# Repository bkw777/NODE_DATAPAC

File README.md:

# NODE Systems DATAPAC
* [Documentation](#documentation)
* [Hardware](#datapac-hardware)
  * [Reproduction Schematic & PCB](#reproduction-schematic--pcb)
  * [Theory of Operation](#theory-of-operation)
  * [Battery](#battery)
  * [Upgrading 128K to 256K](#upgrading-to-256k)
  * [Model Compatibility](#model-compatibility)
* [Software](#software)
  * [BASIC](#basic)
<!-- 
  * [RAMDSK](#ramdsk)
    * [Installation](#installing-ramdsk)
    * [Usage](#using-ramdsk)
  * [NBOOT](#nboot)
  * [RAMPAC Inspector](#rampac-inspector)
  * [XOS-C](#xos-c)
  * [N-DKTR](#n-dktr)
  * [NODE-PDD-Link](#node-pdd-link)
  * [NDEXE](#ndexe)
  * [RAMPAC Diagnostic](#rampac-diagnostic)
-->
* [MiniNDP](#minindp)
<!--
  * [PCB & BOM](#minindp-pcb--bom)
  * [Cover](#minindp-cover)
-->

This repo documents the NODE Systems [DATAPAC](PICS/DATAPAC/), [rampac](PICS/rampac/), and a new clone, the [MiniNDP](#minindp).

The NODE Systems DATAPAC/rampac was a popular ram disk peripheral for TRS-80 / TANDY Models 100, 102, & 200 computers.

The schematic and PCB below documents the DATAPAC.

rampac is a smaller later version of the same device that uses fewer larger sram chips and replaces most of the discrete logic IC's with a single PLD, but functions exactly the same.

Here is some disorganized [INFO](software/) mostly gathered from the [M100SIG archive](https://github.com/LivingM100SIG/Living_M100SIG) and [club100](http://www.club100.org).

TLDR: To use the hardware, install [RAMDSK](software/RAMDSK), and what you get is a ram disk of 128k to 1M depending on model and installed ram.

# Documentation
The original text file manual [RAMDSK.DO](ROM/100/RAMDSK.DO).  
The [NODE ROM](ROM) that came with the unit generates this file when formatting a device.

There are also some discussions in the [M100SIG archive](https://github.com/LivingM100SIG/Living_M100SIG) and Paul Globmans software on [club100](http://www.club100.org/library/libpg.html).  
Most of these are collected in [docs](docs).  
See also the docs for the various bits of [software](software).

Other References  
* "Database management with both the Node RAMPAC & DATAPAC."  
  Alspaugh, Ron - [Portable 100, Nov 90:8-11](https://archive.org/details/P100-Magazine/1990-11/page/8/)  
* "Node utility mini-extravaganza! Here are two special programs for Node Datapac/RAMPAC users."  
  Globman, Paul - [Portable 100, Dec 90:19-20](https://archive.org/details/P100-Magazine/1990-12/page/18/)  

# DATAPAC Hardware
## Reproduction Schematic & PCB
This is a new drawing but aims to reflect the original actual device as exactly as possible.  
It's meant to be a form of documentation or reference describing the original hardware as it was.  
For instance, the ungrounded inputs on the 161's, the inconsistent thickness of power traces, the fact that only 1 of the 2 bus VDD pins is connected, the VCC trace that almost touches one of the mounting screw heads, etc, are all exactly as in the original.  
(I added a fiber washer to that screw in my units after noticing that. The case is not connected to ground, but still...)  

For a historical reproduction version of the original PCB (minus the NODE copyright mark), see: NODE_DATAPAC_256K_historical_reproduction.kicad_pro

For a version of the original PCB that still uses the same components and fits in the same case, but cleans up a few things, see: NODE_DATAPAC_256K_bkw.kicad_pro

PCB TOP

PCB BOTTOM

The original PCB has no silkscreen. This image has silkscreen added to show where the components from the schematic go.

<!--
## Updated Replacement PCB that fits the original case

Uses all the same through-hole parts, fits in the original enclosure, improves the trace routing a little, for example moving that VCC line away from that screw head, GND traces replaced by zone fills, thicker and all the same size vcc lines, decoupling caps, silkscreen.  

-->

## Theory of Operation
The circuit has 2 functions, SELECT-BLOCK and READ/WRITE-BYTE, controlled by the internal active-low signals /BLOCK and /BYTE.

The U4 HC138 monitors four lines from the bus, `/Y0` `(A)` `A8` `A9`, and based on that asserts either `/BLOCK` or `/BYTE` or neither.  
If neither /BLOCK nor /BYTE is asserted then the bus traffic has no effect on any of the other chips.

The 3 HC161 form a 0-1023 counter, setting SRAM address bits A0-A9.  
Call this the byte-number or byte-position counter or offset.

The HC374 sets SRAM address bits A10-A17 from the bus data bits AD0-AD7, and latches that value on its outputs until triggered to update to a new value.  
Call this the block-number or block selector.

The U5 HC138 converts 3 bits of the block-number into 1 of 8 chip-select to select 1 of 8 32K SRAM chips,  
and also monitors both /BYTE and RAMRST and disables all ram while either /BYTE or RAMRST is high.

----

### SELECT-BLOCK
When /BLOCK goes low:
* SRAM A0-A9 are reset to 0  (byte-position counter is reset to 0)
* BUS AD0-AD7 are copied to SRAM A10-A17  (bus data lines AD0-AD7 select a block-number)

When /BLOCK goes high:
* SRAM A10-A17 are held latched at whatever they were set to  (block-number is locked in until next /BLOCK)

----

### READ-BYTE / WRITE-BYTE
When /BYTE goes low:
* SRAM is enabled  (bus data lines AD0-AD7 read from or write to the current address in SRAM)

When /BYTE goes high:
* SRAM is disabled
* A0-A9 are incremented by 1 (byte-position, thus the current address in SRAM, is advanced to the next byte)

----

The byte-number and block-number combine to form the current address in SRAM at any given time.  

The device provides up to 256 blocks (8-bit block-number) of 1024 bytes each (10-bit byte-number).

The host computer first does a SELECT-BLOCK to select a block number from 0-255, then does READ-BYTE or WRITE-BYTE to read or write one byte of data at byte number 0 in that block, then repeats the BYTE operation up to 1023 more times to read or write up to all 1024 bytes in the block.  

If you read or write more than 1024 times without selecting a new block, the byte-number counter just rolls over to 0 again.

You can also mix reads and writes in the same block. Each read OR write advances the byte position the same way each time, regardless if the previous operation was a read or a write. For instance in order to skip over 64 bytes without modifying them and then start writing at the 65th byte, you would read-and-ignore 64 times and then start writing.

"ramdisk" is an appropriate term because the device actually does operate like a disk even though it has no brains or firmware. The block-select latch acts like a track or sector address, and the binary counter acts like a disk or tape head reading or writing a sequential stream of bytes.

Later versions of RAMPAC were offered with 384k or 512k by adding a second bank of up to 256k, and later versions of RAMDSK.CO know how to access the 2nd bank.

In 512K units, the extra 256K is accessed by the state of bus address line A10 during a SELECT-BLOCK operation.  
SELECT-BLOCK with BUS_A10 low accesses bank0, with BUS_A10 high accesses bank1.  
All other aspects are the same, so accessing bank0 on a a 512K device is the same as accessing the only bank on a 256K device.  Old software is still compatible with bank0 on new hardware, new software is still compatible with old hardware.

[What this all means from the host computer software side of things](https://github.com/bkw777/NODE_DATAPAC?tab=readme-ov-file#low-level-direct-access-using-only-basic)

## Battery
The original battery is no longer made, and the modern cross-reference is almost 2mm taller and does not fit inside the enclosure.

NODE Systems themselves used to perform an update to older units to replace the original rechargeable NiCD cell with a non-rechargeable lithium cell which was supposed to last about 5 years.

The change is simple and easy, and the parts are common. You just remove the old battery and the 200 ohm resistor, and replace them with a CR2032 holder and a diode. That's it. Both parts fit and solder right in the same locations where the old parts came out. Point the diode stripe away from the battery, just like the other diode that is right there next to it. Any standard diode will do. Schottky is not recommended because the reverse leakage is not good for a lithium cell. Another 1N4148 like the one that's already there is perfect.  
This should give at least 4 years of memory.  
(The original NiCD battery may have only lasted as little as a few months per charge according to a review in the archives. So the coin cell mod is not merely more conveniently available with current parts, it's an improvement.)

BEFORE

AFTER

STEPS

If you wish to keep using a rechargeable battery, then one suitable option is FL3/V80H. That is 3 16x5.8mm NiMH button cells in a flat in-line pack with wire leads. It fits perfectly in the space next to the ribbon cable. It needs to be secured with hot glue or foam mounting tape, and connected with wires run to the original battery location.  

The charging circuit is utterly basic, so do not connect any other type of battery except NiCD or NiMH.  
You can use any cell form factor and any larger or smaller mAh capacity, but must be 3.6v and only NiCD or NiMH chemistry.

## Upgrading to 256K
A 128k unit may be upgraded to 256k by just adding 4 more SRAM chips piggy-backed onto the existing chips.

The PCB has 4 DIP-28 footprints for the SRAM chips.  
Each DIP-28 footprint also has an extra via close to pin 20.

A 128k unit has a low-power 62256 installed in each footprint, and nothing connected to the via near pin 20.

To get 256k, a second set of chips are soldered piggyback on top of the first four.  
All pins except pin 20 (chip-select) are simply soldered to the chip below.  
Pin 20 is bent out and connected to the extra via on the pcb (with a short bit of wire to reach) and not connected to the chip below.  

No other parts or changes are needed to upgrade an existing 128k unit to 256k.

Any 62256 will work, but for old parts you want the low-power version for standby battery life.  
New parts already naturally have as low or lower standby current than the low-power versions of old parts even if they don't say "low power".  
Old standard: HM62256    70uA  
Old lowpower: HM62256LP  4uA  
Old lowpower: P51256SL   2uA  
New standard: AS6C62256  1uA

The same is true for rampac. Except:  
 - single 128k sram chip, ex: AS6C1008
 - chip-select is pin 30

## Model compatibility  
Originally only North-American Models 100, 102, & 200 were ever supported.  
Kyotronic KC-85 and Olivetti M-10 are also supported today because RAMDSK has been disassembled and ported, and the assembly source means the international models could be added as well.  
The device is not compatible with NEC PC-8201/PC-8300.

Although the DATAPAC was primarily designed for Model 102 & 200, the crimp-on boxed male IDC pin header on the cable does not actually fit into a 200 without enlarging the opening around the bus connector on the 200. If you want to connect an original DATAPAC to a 200 without hacking up the 200's case or modifying the DATAPAC cable, you can build a small [adapter](ref/T200_adapter.jpg) by just soldering a [male](https://www.digikey.com/en/products/detail/sullins-connector-solutions/SBH11-PBPC-D20-ST-BK/1990068) & [female](https://www.digikey.com/en/products/detail/sullins-connector-solutions/SFH11-PBPC-D20-ST-BK/1990093) solder-type 2x20 boxed pin headers back to back. The solder box header does fit in the opening.

The DATAPAC case says "102/200", but it also works on Model 100, K85, and M10 with the right adapter cable. It's electrically compatible with everything but NEC.

For 100 & K85 the cable is just an IDC-DIP-40 aka "DIP-40 wire-to-board" connector and a standard 2x20 female IDC connector, both crimped onto a 40-pin ribbon cable about 8 inches long.  
[The Model 100 adapter part](https://github.com/bkw777/TRS-80_Disk_Video_Interface_Cable/blob/main/README.md#part-3---model-100-adapter) of this [3-part Disk/Video Interface Cable](http://tandy.wiki/Disk/Video_Interface:_Cable) is the same thing.

For Olivetti M-10 the cable is even simpler, a standard female to female IDC 40-pin ribbon cable.

[MiniNDP](#minindp) fits directly on both 102 and 200 with no adapter or cable, or M10 with a female-female ribbon cable at least 5 inches long.

[MiniNDP_u1M](#minindp-u1m---for-model-100-or-kyotronic-kc-85) fits directly in the bus socket of 100 or K85 with no adapter or cable, and the cover can even be closed over it.

# Software

 - [NODE ROM](ROM)  
 - [RAMDSK.CO](software/RAMDSK)  
 - [XOS-C](http://www.club100.org/library/libpg.html) ("sort of an OS" for the Model 200, does not require a rampac but leverages one if available. [Several of the NODE utils from the M100SIG require XOS-C.](software/Requires_XOS-C/))
 - [other](software)  

Originally these shipped with an [OPTION ROM](ROM) from NODE called RAMDISK.

Later, Paul Globman wrote [RAMDSK.CO](software/RAMDSK), and that was eventually licensed by NODE and shipped with new units.  

Later still, RAMDSK was updated with 2 changes:  
 - automatic repair of a corrupted format stamp on start-up  
 - support for 512k in 2 banks of 256k (RAMPAC & EXTRAM)

Recently, RAMDSK has been updated yet further:  
- disassembled to produce assembly source  
- ported to Kyotronic KC-85  
- ported to Olivetti M-10  
- support for 4 banks  
- format on demand from Label button  
- added safety confirmation to format & repair  
- removed dead code

Some other software culled from the [M100SIG archive](https://github.com/LivingM100SIG/Living_M100SIG) and [Club100](https://www.club100.org) are collected here in the [software](software) directory.  

## BASIC
How to access the hardware from BASIC.

### High level file operations using CALLable machine language routines
See [RAMDSK.DO](ROM/100/RAMDSK.DO) for the NODE ROM routines.  
See [RAMDSK.TIP](software/RAMDSK/RAMDSK.TIP) for the RAM100.CO/RAM200.CO routines.  
But note, the addresses in RAMDSK.TIP are incorrect for RAMDSK v2. We don't have a copy of RAMDSK v1 for 100 but we do for 200. So you can't follow those directions exactly except with RAMDSK v1 on 200.  

The latest RAMDSK built from the new source includes *.calls files that give the current addresses to the routines in those binaries, but actually using them has not been tested.

### Low level direct access using only BASIC
There are two low level operations that you use to access the device,  
BLOCK and BYTE, and each of those has two variations, for four total ops.

Select a BLOCK from BANK 0  
`OUT 129,n`  
Selects block# **n** (0-255) in bank 0, and resets the byte position to 0.

Select a BLOCK from BANK 1  
`OUT 133,n`  
Selects block# **n** (0-255) in bank 1, and resets the byte position to 0.

Read a BYTE  
`INP(131)`  
Reads the byte at the current byte position, and advances the byte position by one.

Write a BYTE  
`OUT 131,n`  
Writes the value **n** (0-255) to the current byte position, and advances the byte position by one.

The first read or write after selecting a block# applies to byte #0 of that block.  
The byte position advances by one after each read or write, so the next read or write will be byte #1, then byte #2, etc up to 1024.  
If you read or write more than 1024 times without selecting some other block, the byte position just rolls over to 0 again.

The position counter advances the same whether reading or writing.

Since the device can only read or write a single unsigned byte at a time, it's most efficient to use integer variables.  
Use the % suffix or DEFINT: `B%=INP(131)` or `DEFINT B : B=INP(131)`

The general sequence is always:  
1 - select a bank+block  
2 - read/write byte 0-1024 times

To seek to an arbitrary offset before reading or writing, read-and-ignore that many bytes.

For instance, in RBOOT.DO, to skip over the first 16 bytes of the block, it does `FORA=0TO15:N=INP(131):NEXT`  
N is not actually used, it's just reading 16 times and ignoring the data. This just advances the byte position counter to get from byte #0 past the 10-byte RAMDSK header and 6-byte .CO header to the start of the .CO executable data.

Examples

Select bank 0 block 0  
`OUT129,0`

read a byte, which will be byte #0 of this block  
`INP(131)`

Read and print the ascii of all the bytes in bank 0 block 2.  
(this will mess up the display from control bytes if there is a binary .CO file in this block)
```
10 OUT 129,2
20 FOR I=0 TO 1023
30 PRINT CHR$(INP(131));
40 NEXT
```

Do the same but in bank 1  
change line 10 to:  
`10 OUT 133,2`

Manually repair the first two bytes of block 0 to mark the bank as being formatted without touching any of the data.  
This means:
1. Select bank0 block0  
2. write one byte, value 64  
3. write one byte, value 4

`OUT129,0:OUT131,64:OUT131,4`

(BTW you usually don't need to do this because RAMDSK.CO will do it for you.)

# MiniNDP

New design that functions the same as DATAPAC/rampac.

1 megabyte in 4 banks of 256k.

How to access all 4 banks:  
Select bank 0, block N: `OUT 129,N`  
Select bank 1, block N: `OUT 133,N`  
Select bank 2, block N: `OUT 137,N`  
Select bank 3, block N: `OUT 141,N`

Everything else works the same as normal DATAPAC/rampac.

## MiniNDP EZ1M - For Model 102 and 200

Unlike the original DATAPAC, this actually fits into the bus port on the Model 200 without having to hack it's case.

[MiniNDP.bom.csv](PCB/out/MiniNDP.bom.csv)

BOM: [DigiKey](https://www.digikey.com/short/m4h7bmh0)  
[MiniNDP EZ1M_16 PCB @ OSHPark](https://oshpark.com/shared_projects/7Jpm6F6c)  
Cover: [MiniNDP_Cover.stl](COVER/out/MiniNDP_Cover.stl) -- [Cover @ JawsTec](https://shop.jawstec.com/3d-printed-minindp-cover_p658.php)  
[Both PCB & Cover @ PCBWAY](https://www.pcbway.com/project/shareproject/MiniNDP_mini_Node_DataPac_d08018c4.html)  

## MiniNDP u1M - For Model 100 or Kyotronic KC-85

BOM: [MiniNDP_u1M.bom.csv](PCB/out/MiniNDP_u1M.bom.csv)  
[MiniNDP u1M_038 PCB @ OSHPark](https://oshpark.com/shared_projects/XwUDgfQu)

## MiniNDP M10 - For Olivetti M-10

BOM: [MiniNDP_M10.bom.csv](PCB/out/MiniNDP_M10.bom.csv)  
[MiniNDP M10_40 PCB @ OSHPark](https://oshpark.com/shared_projects/pgmxRV8e)  
Cover for M10: [MiniNDP_Cover_M10.stl](COVER/out/MiniNDP_Cover_M10.stl) -- [M10 Cover @ JawsTec](https://shop.jawstec.com/3d-printed-minindpm10-cover_p657.php)  
Bus connector guide & filler plate for M10 [M10_BUS_Filler_Plate.stl](COVER/out/M10_BUS_Filler_Plate.stl)

## [Other Versions](MiniNDP_variants.md)  
[SL1M](MiniNDP_variants.md#sl1m---slim-1-meg) - slim 1 meg, all thin chips to make a thin card  
[T512](MiniNDP_variants.md#t512---tsop-128k256k512k) - TSOP 128k/256k/512k  
[EZ512](MiniNDP_variants.md#ez512---easy-build-512k) - SOIC 512k  
<!-- ["OG"](MiniNDP_variants.md#minindp-og) - 128k-512k, most like the original DATAPAC schematic, more parts and more difficult, but the parts are more common  -->

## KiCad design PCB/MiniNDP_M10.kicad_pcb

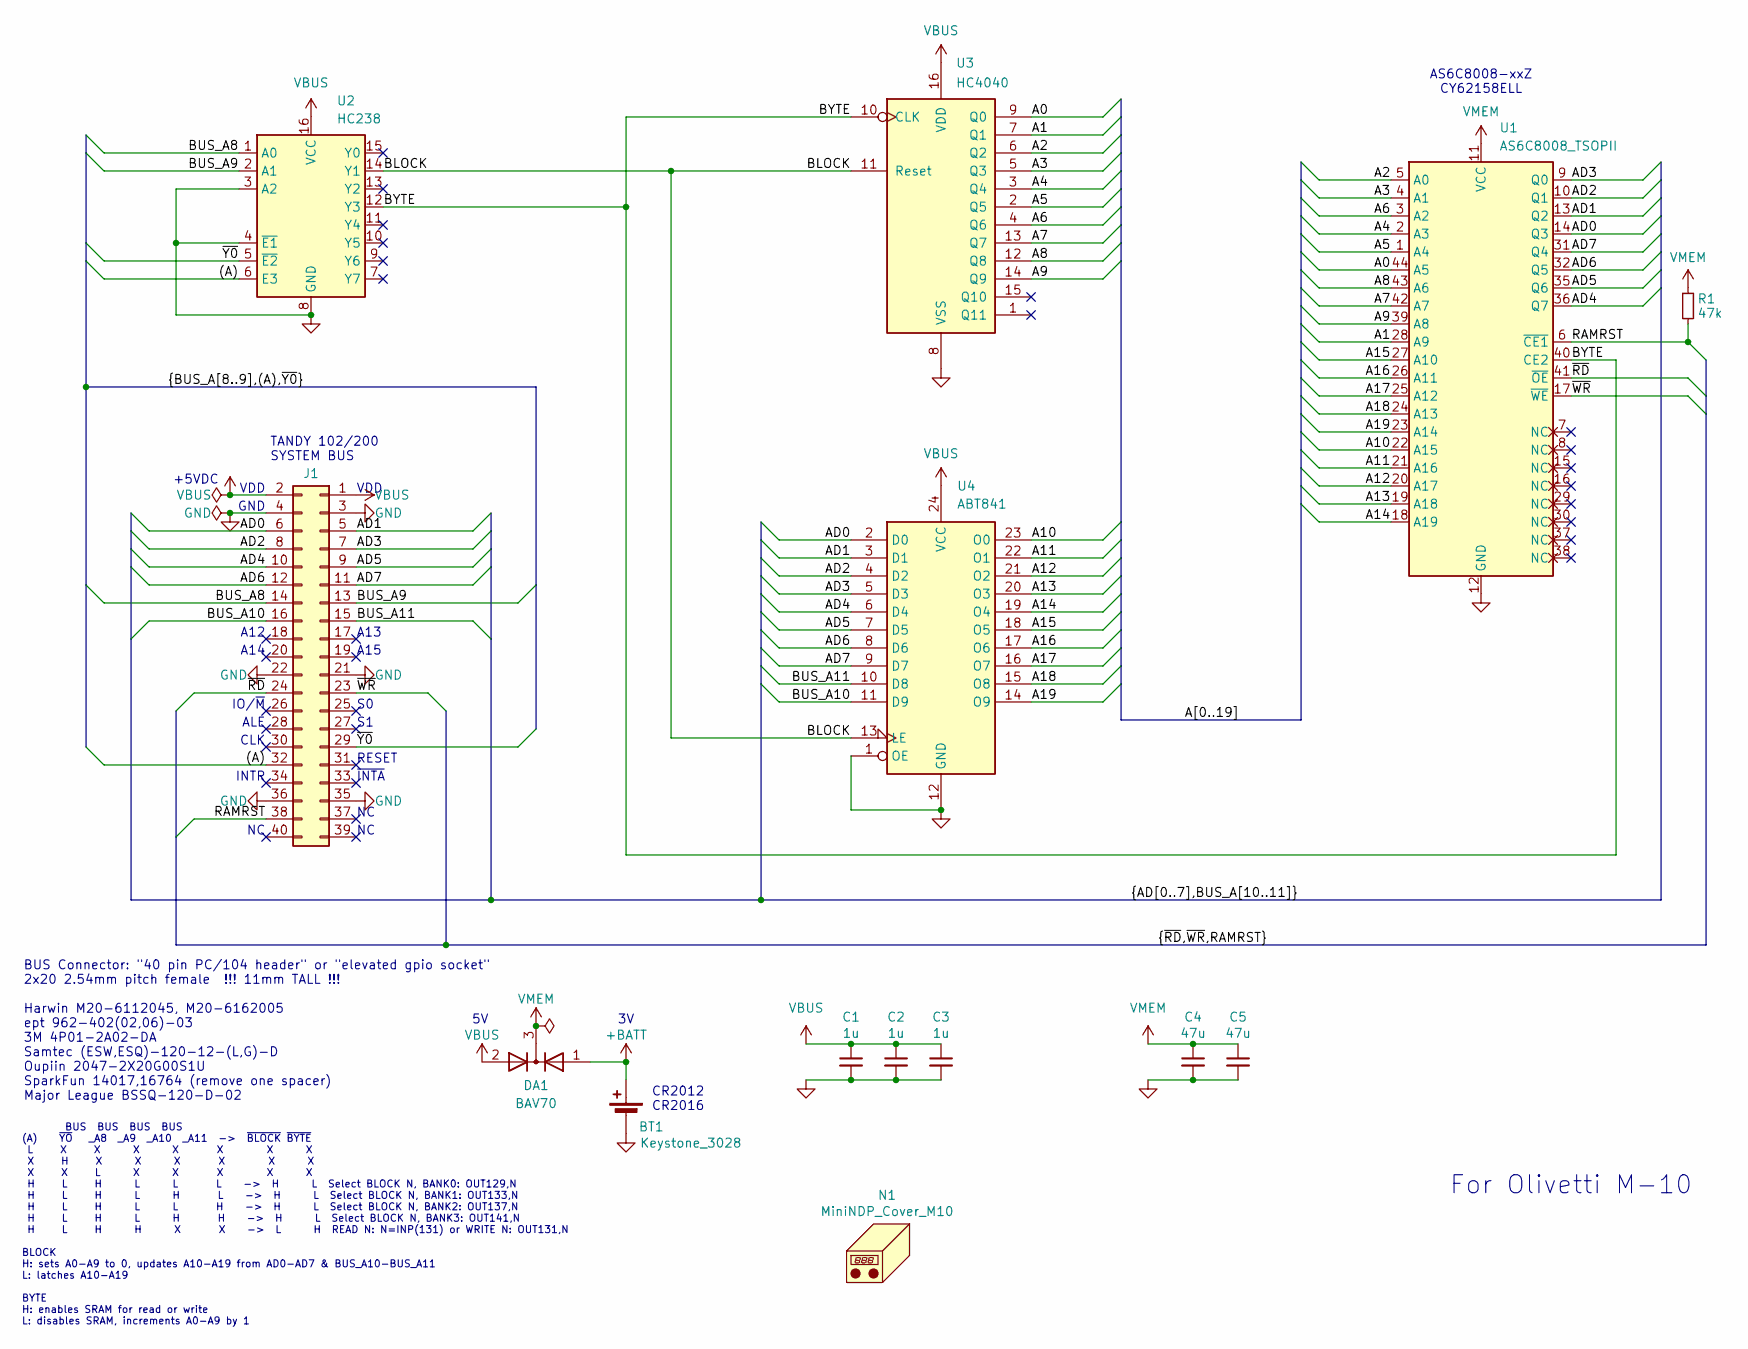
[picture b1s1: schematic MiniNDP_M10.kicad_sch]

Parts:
BT1: Keystone_3028; Keystone_3028_3034_bkw; MPN Keystone 3028
C1, C2, C3: 1u; C_0805; MPN CL21B105KAFNNNE
C4, C5: 47u; C_1206; MPN C3216X5R1E476M160DC
DA1: BAV70; SOT-23; MPN BAV70-7-F
J1: Conn_02x20_Odd_Even; PinSocket_2x20_P2.54mm_Vertical; MPN M20-6112045
N1: MiniNDP_Cover_M10; MPN MiniNDP_Cover_M10.stl
R1: 47k; R_0805; MPN RMCF0805FT47K0
U1: AS6C8008_TSOPII; TSOP-II-44; MPN AS6C8008-55ZIN
U2: HC238; TSSOP-16; MPN 74HC238PW,118
U3: HC4040; TSSOP-16; MPN 74HC4040PW,118
U4: ABT841; TSSOP-24; MPN SN74ABT841APW

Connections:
+BATT: BT1.1 (+), DA1.1 (A)
/(A): J1.32, U2.6 (E3)
/A0: U1.44 (A5), U3.9 (Q0)
/A1: U1.28 (A9), U3.7 (Q1)
/A2: U1.5 (A0), U3.6 (Q2)
/A3: U1.4 (A1), U3.5 (Q3)
/A4: U1.2 (A3), U3.3 (Q4)
/A5: U1.1 (A4), U3.2 (Q5)
/A6: U1.3 (A2), U3.4 (Q6)
/A7: U1.42 (A7), U3.13 (Q7)
/A8: U1.43 (A6), U3.12 (Q8)
/A9: U1.39 (A8), U3.14 (Q9)
/A10: U1.22 (A15), U4.23 (O0)
/A11: U1.21 (A16), U4.22 (O1)
/A12: U1.20 (A17), U4.21 (O2)
/A13: U1.19 (A18), U4.20 (O3)
/A14: U1.18 (A19), U4.19 (O4)
/A15: U1.27 (A10), U4.18 (O5)
/A16: U1.26 (A11), U4.17 (O6)
/A17: U1.25 (A12), U4.16 (O7)
/A18: U1.24 (A13), U4.15 (O8)
/A19: U1.23 (A14), U4.14 (O9)
/AD0: J1.6, U1.14 (Q3), U4.2 (D0)
/AD1: J1.5, U1.13 (Q2), U4.3 (D1)
/AD2: J1.8, U1.10 (Q1), U4.4 (D2)
/AD3: J1.7, U1.9 (Q0), U4.5 (D3)
/AD4: J1.10, U1.36 (Q7), U4.6 (D4)
/AD5: J1.9, U1.35 (Q6), U4.7 (D5)
/AD6: J1.12, U1.32 (Q5), U4.8 (D6)
/AD7: J1.11, U1.31 (Q4), U4.9 (D7)
/BLOCK: U2.14 (Y1), U3.11 (Reset), U4.13 (LE)
/BUS_A8: J1.14, U2.1 (A0)
/BUS_A9: J1.13, U2.2 (A1)
/BUS_A10: J1.16, U4.11 (D9)
/BUS_A11: J1.15, U4.10 (D8)
/BYTE: U1.40 (CE2), U2.12 (Y3), U3.10 (CLK)
/RAMRST: J1.38, R1.2, U1.6 (~CE1)
/~RD: J1.24, U1.41 (~OE)
/~WR: J1.23, U1.17 (~WE)
/~Y0: J1.29, U2.5 (~E2)
GND: BT1.2 (-), C1.2, C2.2, C3.2, C4.2, C5.2, J1.3, J1.4, J1.21, J1.22, J1.35, J1.36, U1.12 (GND), U1.34 (GND), U2.3 (A2), U2.4 (~E1), U2.8 (GND), U3.8 (VSS), U4.1 (OE), U4.12 (GND)
VBUS: C1.1, C2.1, C3.1, DA1.2 (A), J1.1, J1.2, U2.16 (VCC), U3.16 (VDD), U4.24 (VCC)
VMEM: C4.1, C5.1, DA1.3 (K), R1.1, U1.11 (VCC), U1.33 (VCC)

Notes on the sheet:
INTR
BUS BUS BUS BUS (A) ~{YO} _A8 _A9 _A10 _A11 -> ~{BLOCK} ~{BYTE} L X X X X X X X X H X X X X X X X X L X X X X X H L H L L L -> H L Select BLOCK N, BANK0: OUT129,N H L H L H L -> H L Select BLOCK N, BANK1: OUT133,N H L H L L H -> H L Select BLOCK N, BANK2: OUT137,N H L H L H H -> H L Select BLOCK N,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
VDD
A14
CLK
~{INTA}
A12
A15
ALE
For Olivetti M-10
A13
GND
IO/~{M}
RESET
AS6C8008-xxZ CY62158ELL
BUS Connector: "40 pin PC/104 header" or "elevated gpio socket" 2x20 2.54mm pitch female !!! 11mm TALL !!! Harwin M20-6112045, M20-6162005 ept 962-402(02,06)-03 3M 4P01-2A02-DA Samtec (ESW,ESQ)-120-12-(L,G)-D Oupiin 2047-2X20G00S1U SparkFun 14017,16764 (remove one spacer) Major League BSSQ-120-D-02
+5VDC
TANDY 102/200 SYSTEM BUS
CR2012 CR2016

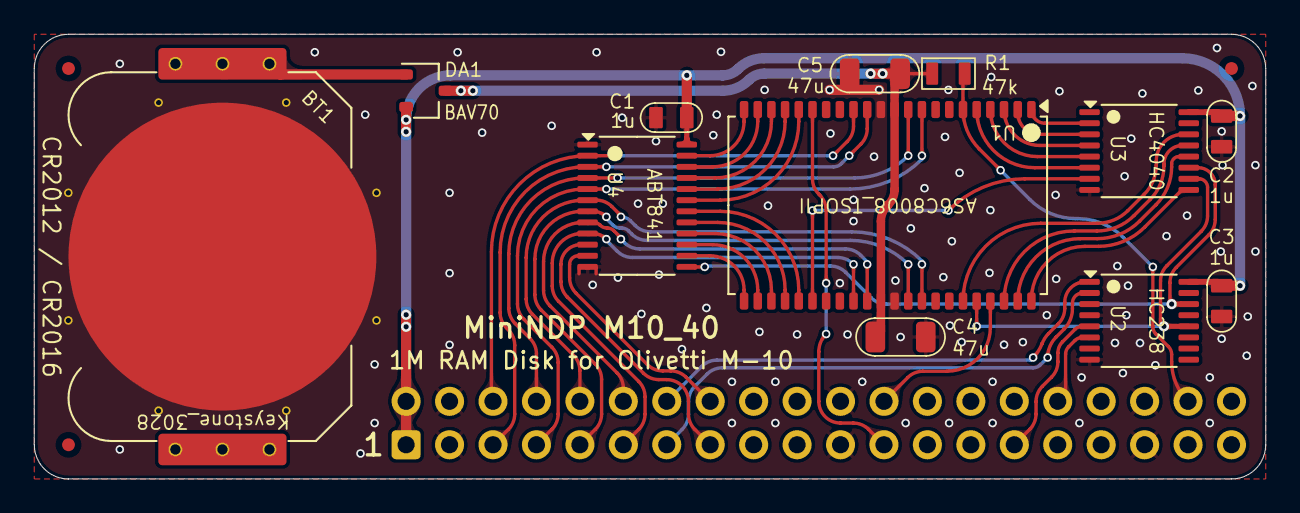
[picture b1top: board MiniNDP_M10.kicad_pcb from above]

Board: 2 copper layers, 72.0 x 26.0 mm, 17 parts (1 on the bottom side), 43 nets.

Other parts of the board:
F3, F3#2, F3#3: Fiducial_0.75_1.5

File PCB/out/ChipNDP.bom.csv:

"Reference","Value","Datasheet","Footprint","Qty","DNP","MPN","Description"
"BT1","Keystone_3031","datasheet/Keystone_3031.pdf","000_LOCAL:Keystone_3031","1","","Keystone 3031","Battery Retainer Coin, 10.0mm 1 Cell PC Pin"
"C1,C2,C3","1u","datasheets/CL21B105KAFNNNE.pdf","000_LOCAL:C_0805","3","","CL21B105KAFNNNE","CAP CER 1UF 25V X7R 0805"
"C4","47u","datasheets/TDK_MLCC_Cxxxx.pdf","000_LOCAL:C_1206","1","","C3216X5R1E476M160DC","CAP CER 47UF 25V X5R 1206"
"DA1","BAV70","datasheets/BAV70.pdf","000_LOCAL:SOT-23","1","","BAV70-7-F","DIODE ARRAY GP 75V 150MA SOT23-3"
"J1","Model_100_System_BUS","datasheets/TRS-80_Model_100_User_Guide.pdf","000_LOCAL:DIP-40_PCB","1","","920-0172-01","CONN HEADER VERT 40P 2.54MM"
"R1","47k","datasheets/sei-rmcf_rmcp.pdf","000_LOCAL:R_0805","1","","RMCF0805FT47K0","RES 47K OHM 1% 1/8W 0805"
"U1","AS6C8008_TSOPII","datasheets/AS6C8008.pdf","000_LOCAL:TSOP-II-44","1","","AS6C8008-55ZIN","IC SRAM 1Mx8 PARALLEL 5v TSOP-II-44"
"U2","HC238","datasheets/HC238.pdf","000_LOCAL:TSSOP-16","1","","74HC238PW,118","IC DECODER/DEMUX 1 X 3:8 16SO"
"U3","HC4040","datasheets/4040.pdf","000_LOCAL:TSSOP-16","1","","74HC4040PW,118","IC BINARY COUNTER 12-BIT 16SO"
"U4","ABT841","datasheets/sn54abt841.pdf","000_LOCAL:TSSOP-24_4.4x7.8mm_P0.65mm","1","","SN74ABT841APW","IC 10BIT LATCH 3-STATE 24-SOIC"

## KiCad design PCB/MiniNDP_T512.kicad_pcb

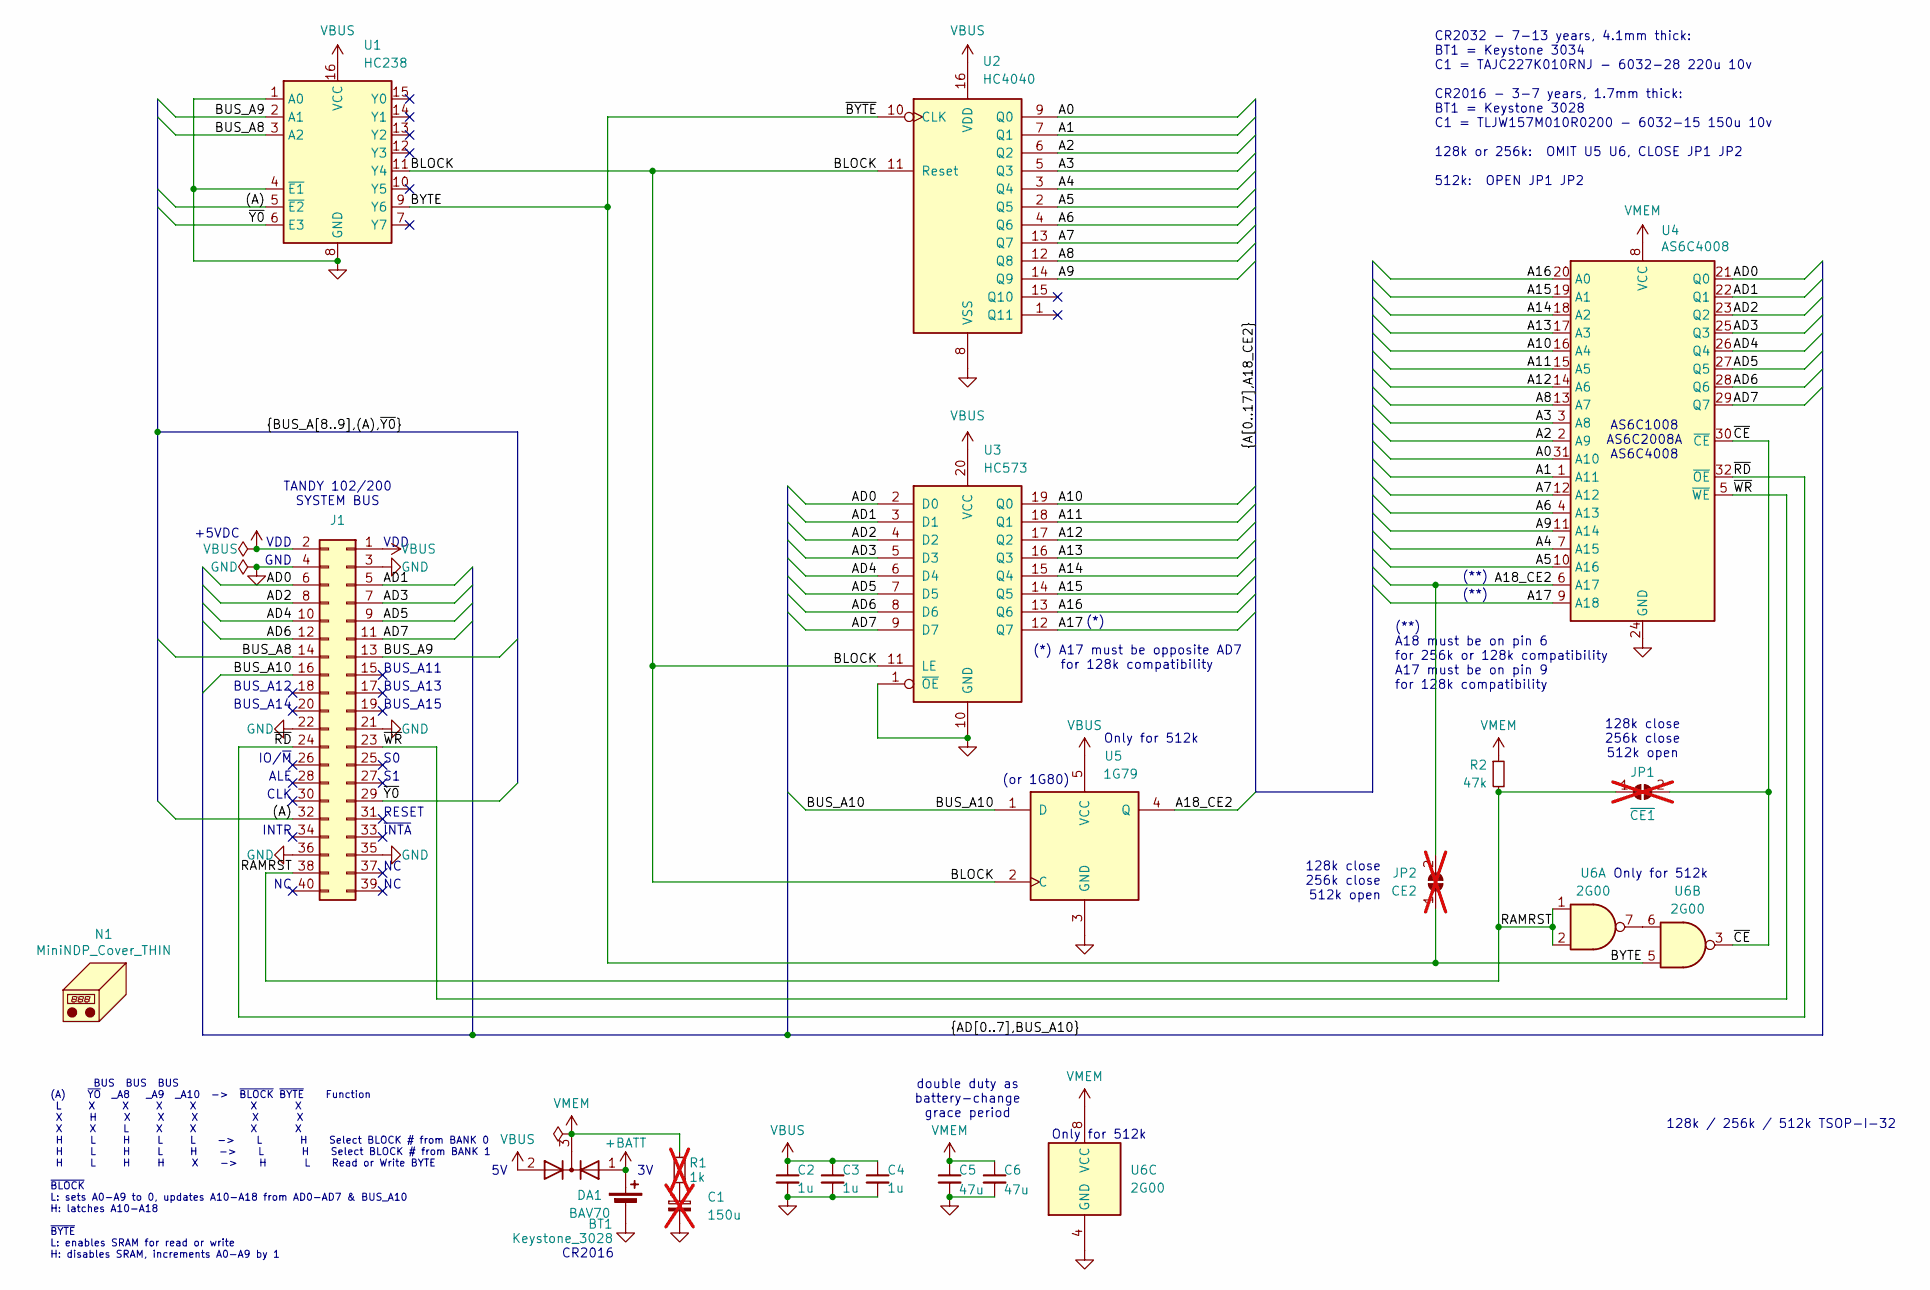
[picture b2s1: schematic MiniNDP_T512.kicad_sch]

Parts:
BT1: Keystone_3028; Keystone_3028_3034_bkw; MPN Keystone_3028
C1: 150u; CP_6032; MPN TLJW157M010R0200; not fitted
C2, C3, C4: 1u; C_0805; MPN CL21B105KAFNNNE
C5, C6: 47u; C_1206; MPN C3216X5R1E476M160DC
DA1: BAV70; SOT-23; MPN BAV70-7-F
J1: Conn_02x20_Odd_Even; IDC-Header_2x20_P2.54mm_Vertical; MPN 302-S401
JP1: ~{CE1}; SolderJumper-2_P1.3mm_Open_RoundedPad1.0x1.5mm; not fitted
JP2: CE2; SolderJumper-2_P1.3mm_Open_RoundedPad1.0x1.5mm; not fitted
N1: MiniNDP_Cover_THIN; MPN MiniNDP_Cover_THIN.stl
R1: 1k; R_0805; MPN RK73B2ATTD102J; not fitted
R2: 47k; R_0805; MPN RMCF0805FT47K0
U1: HC238; TSSOP-16; MPN 74HC238PW,118
U2: HC4040; TSSOP-16; MPN 74HC4040PW,118
U3: HC573; TSSOP-20; MPN 74HC573PW,118
U4: AS6C4008; TSOP32-dual; MPN AS6C4008-55STIN
U5: 1G79; SOT-353_SC-70-5; MPN 74LVC1G79GW,125
U6: 2G00; TSSOP-8_3x3mm_P0.65mm

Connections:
+BATT: BT1.1 (+), DA1.1 (A)
/(A): J1.32, U1.5 (~E2)
/A0: U2.9 (Q0), U4.31 (A10)
/A1: U2.7 (Q1), U4.1 (A11)
/A2: U2.6 (Q2), U4.2 (A9)
/A3: U2.5 (Q3), U4.3 (A8)
/A4: U2.3 (Q4), U4.7 (A15)
/A5: U2.2 (Q5), U4.10 (A16)
/A6: U2.4 (Q6), U4.4 (A13)
/A7: U2.13 (Q7), U4.12 (A12)
/A8: U2.12 (Q8), U4.13 (A7)
/A9: U2.14 (Q9), U4.11 (A14)
/A10: U3.19 (Q0), U4.16 (A4)
/A11: U3.18 (Q1), U4.15 (A5)
/A12: U3.17 (Q2), U4.14 (A6)
/A13: U3.16 (Q3), U4.17 (A3)
/A14: U3.15 (Q4), U4.18 (A2)
/A15: U3.14 (Q5), U4.19 (A1)
/A16: U3.13 (Q6), U4.20 (A0)
/A17: U3.12 (Q7), U4.9 (A18)
/A18_CE2: JP2.2 (B), U4.6 (A17), U5.4 (Q)
/AD0: J1.6, U3.2 (D0), U4.21 (Q0)
/AD1: J1.5, U3.3 (D1), U4.22 (Q1)
/AD2: J1.8, U3.4 (D2), U4.23 (Q2)
/AD3: J1.7, U3.5 (D3), U4.25 (Q3)
/AD4: J1.10, U3.6 (D4), U4.26 (Q4)
/AD5: J1.9, U3.7 (D5), U4.27 (Q5)
/AD6: J1.12, U3.8 (D6), U4.28 (Q6)
/AD7: J1.11, U3.9 (D7), U4.29 (Q7)
/BLOCK: U1.11 (Y4), U2.11 (Reset), U3.11 (LE), U5.2 (C)
/BUS_A8: J1.14, U1.3 (A2)
/BUS_A9: J1.13, U1.2 (A1)
/BUS_A10: J1.16, U5.1 (D)
/BYTE: JP2.1 (A), U1.9 (Y6), U2.10 (CLK), U6.5
/RAMRST: J1.38, JP1.1 (A), R2.2, U6.1, U6.2
/~CE: JP1.2 (B), U4.30 (~CE), U6.3
/~RD: J1.24, U4.32 (~OE)
/~WR: J1.23, U4.5 (~WE)
/~Y0: J1.29, U1.6 (E3)
GND: BT1.2 (-), C1.2, C2.2, C3.2, C4.2, C5.2, C6.2, J1.3, J1.4, J1.21, J1.22, J1.35, J1.36, U1.1 (A0), U1.4 (~E1), U1.8 (GND), U1.24, U2.8 (VSS), U3.1 (~OE), U3.10 (GND), U4.24 (GND), U5.3 (GND), U6.4 (GND)
unnamed: C1.1, R1.2
unnamed: U6.6, U6.7
VBUS: C2.1, C3.1, C4.1, DA1.2 (A), J1.1, J1.2, U1.16 (VCC), U2.16 (VDD), U3.20 (VCC), U5.5 (VCC)
VMEM: C5.1, C6.1, DA1.3 (K), R2.1, U4.8 (VCC), U6.8 (VCC)

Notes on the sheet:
TANDY 102/200 SYSTEM BUS
+5VDC
BUS_A15
INTR
BUS_A14
128k close 256k close 512k open
ALE
(**)
AS6C1008 AS6C2008A AS6C4008
~{INTA}
CLK
(**) A18 must be on pin 6 for 256k or 128k compatibility A17 must be on pin 9 for 128k compatibility
CR2032 - 7-13 years, 4.1mm thick: BT1 = Keystone 3034 C1 = TAJC227K010RNJ - 6032-28 220u 10v CR2016 - 3-7 years, 1.7mm thick: BT1 = Keystone 3028 C1 = TLJW157M010R0200 - 6032-15 150u 10v 128k or 256k: OMIT U5 U6, CLOSE JP1 JP2 512k: OPEN JP1 JP2
GND
IO/~{M}
Only for 512k
CR2016
(or 1G80)
VDD
128k / 256k / 512k TSOP-I-32
BUS BUS BUS (A) ~{YO} _A8 _A9 _A10 -> ~{BLOCK} ~{BYTE} Function L X X X X X X X H X X X X X X X L X X X X H L H L L -> L H Select BLOCK # from BANK 0 H L H L H -> L H Select BLOCK # from BANK 1 H L H H X -> H L Read or Write BYTE ~{BLOCK} L: sets A0-A9 to 0, updates A10-A18 from AD0-AD7 & BUS_A10 H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
RESET
(*) A17 must be opposite AD7 for 128k compatibility
BUS_A11
BUS_A13
double duty as battery-change grace period
(*)
BUS_A12

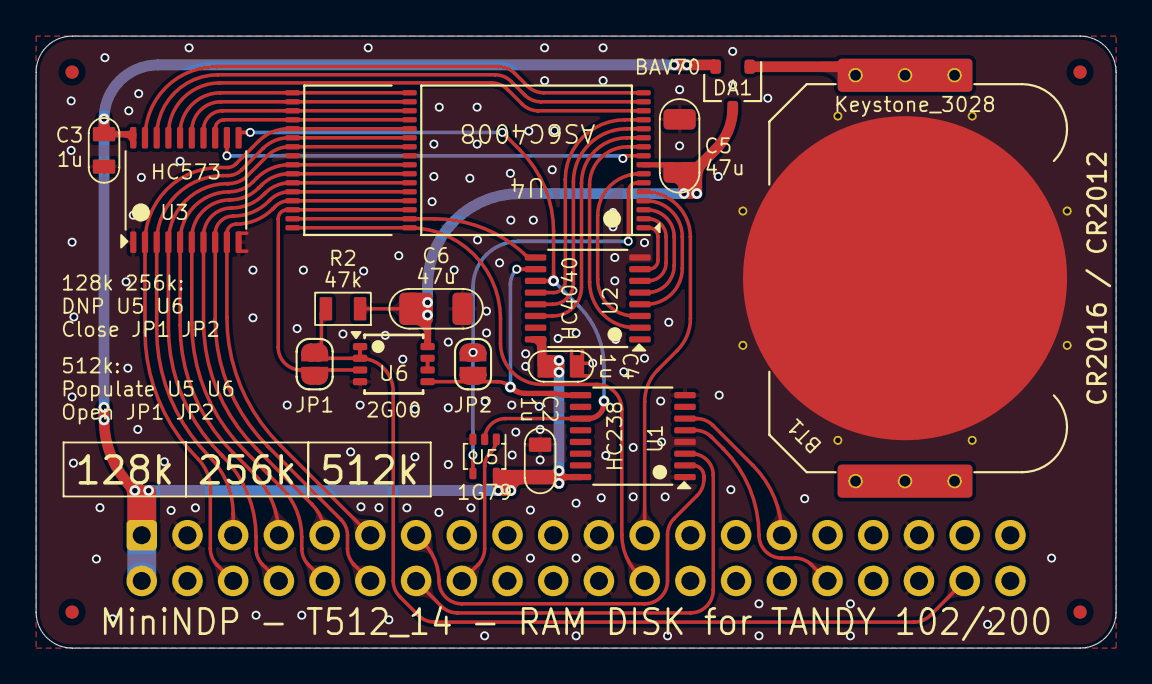
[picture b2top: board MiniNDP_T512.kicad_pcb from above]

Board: 2 copper layers, 60.0 x 34.0 mm, 22 parts (1 on the bottom side), 43 nets.

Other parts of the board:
F3, F3#2, F3#3, F3#4: Fiducial_0.75_1.5

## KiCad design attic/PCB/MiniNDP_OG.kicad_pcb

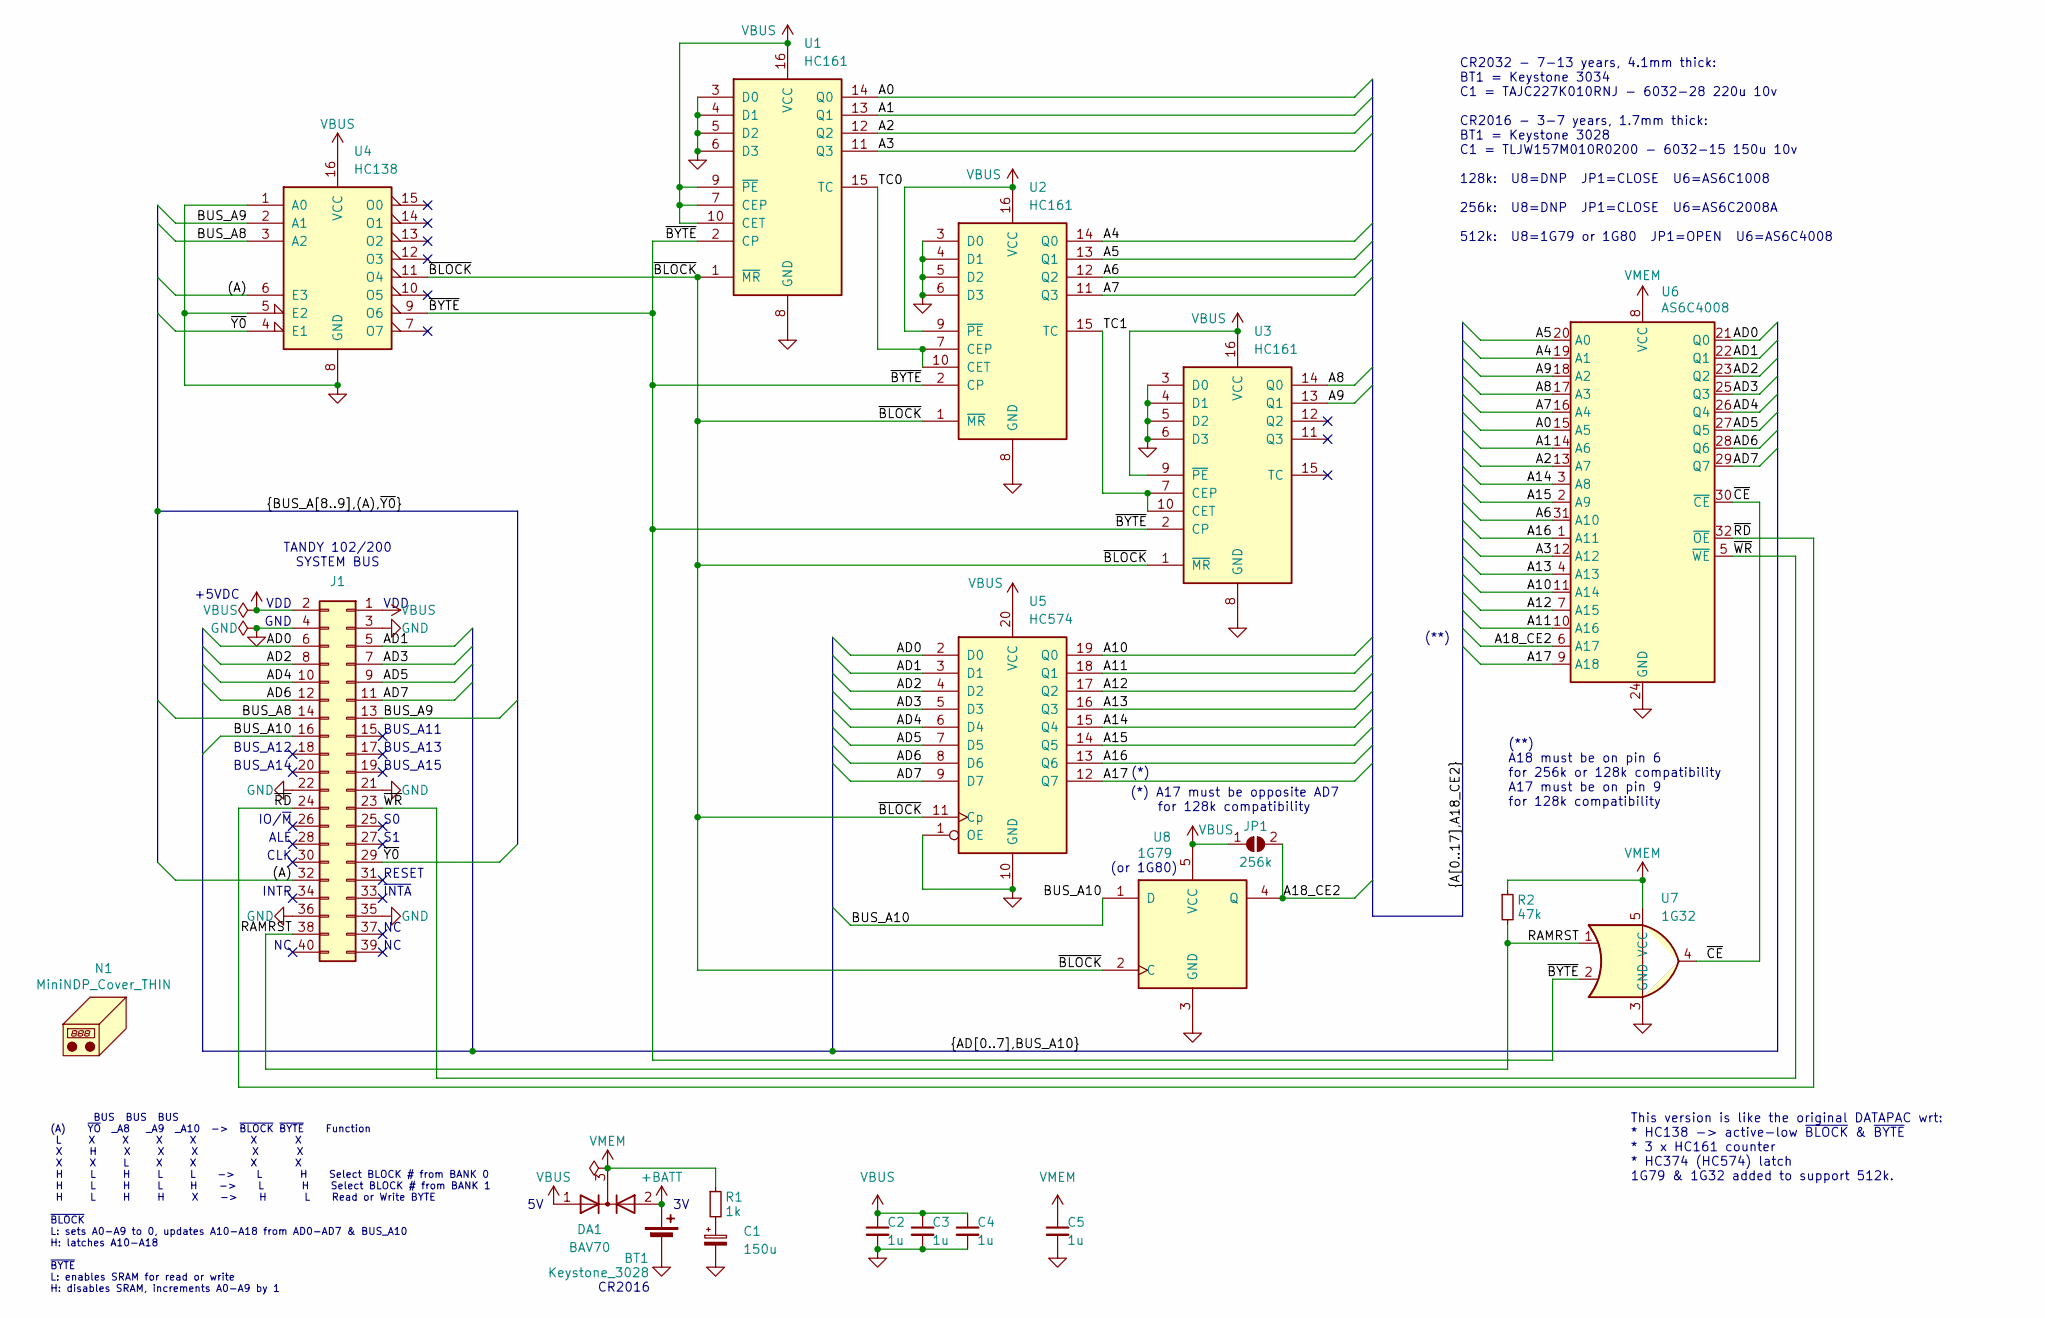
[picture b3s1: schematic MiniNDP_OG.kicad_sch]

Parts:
BT1: Keystone_3028; Keystone_3028_3034_bkw; MPN Keystone_3028
C1: 150u; CP_6032; MPN TLJW157M010R0200
C2, C3, C4, C5: 1u; C_0805; MPN CL21B105KAFNNNE
DA1: BAV70; SOT-23; MPN BAV70-7-F
J1: Conn_02x20_Odd_Even; IDC-Header_2x20_P2.54mm_Vertical; MPN 302-S401
JP1: 256k; SolderJumper-2_Open 0.65mm
N1: MiniNDP_Cover_THIN; MPN MiniNDP_Cover_THIN.stl
R1: 1k; R_0805; MPN RK73B2ATTD102J
R2: 47k; R_0805; MPN RMCF0805FT47K0
U1, U2, U3: HC161; TSSOP-16; MPN 74HC161PW,118
U4: HC138; TSSOP-16; MPN 74HC138PW,118
U5: HC574; TSSOP-20; MPN 74HC574PW,118
U6: AS6C4008; TSOP32-dual; MPN AS6C4008-55STIN
U7: 1G32; SOT-353_SC-70-5; MPN 74LVC1G32GW,125
U8: 1G79; SOT-353_SC-70-5; MPN 74LVC1G79GW,125

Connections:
+BATT: BT1.1 (+), DA1.2 (A)
/(A): J1.32, U4.6 (E3)
/A0: U1.14 (Q0), U6.15 (A5)
/A1: U1.13 (Q1), U6.14 (A6)
/A2: U1.12 (Q2), U6.13 (A7)
/A3: U1.11 (Q3), U6.12 (A12)
/A4: U2.14 (Q0), U6.19 (A1)
/A5: U2.13 (Q1), U6.20 (A0)
/A6: U2.12 (Q2), U6.31 (A10)
/A7: U2.11 (Q3), U6.16 (A4)
/A8: U3.14 (Q0), U6.17 (A3)
/A9: U3.13 (Q1), U6.18 (A2)
/A10: U5.19 (Q0), U6.11 (A14)
/A11: U5.18 (Q1), U6.10 (A16)
/A12: U5.17 (Q2), U6.7 (A15)
/A13: U5.16 (Q3), U6.4 (A13)
/A14: U5.15 (Q4), U6.3 (A8)
/A15: U5.14 (Q5), U6.2 (A9)
/A16: U5.13 (Q6), U6.1 (A11)
/A17: U5.12 (Q7), U6.9 (A18)
/A18_CE2: JP1.2 (B), U6.6 (A17), U8.4 (Q)
/AD0: J1.6, U5.2 (D0), U6.21 (Q0)
/AD1: J1.5, U5.3 (D1), U6.22 (Q1)
/AD2: J1.8, U5.4 (D2), U6.23 (Q2)
/AD3: J1.7, U5.5 (D3), U6.25 (Q3)
/AD4: J1.10, U5.6 (D4), U6.26 (Q4)
/AD5: J1.9, U5.7 (D5), U6.27 (Q5)
/AD6: J1.12, U5.8 (D6), U6.28 (Q6)
/AD7: J1.11, U5.9 (D7), U6.29 (Q7)
/BUS_A8: J1.14, U4.3 (A2)
/BUS_A9: J1.13, U4.2 (A1)
/BUS_A10: J1.16, U8.1 (D)
/RAMRST: J1.38, R2.2, U7.1
/TC0: U1.15 (TC), U2.7 (CEP), U2.10 (CET)
/TC1: U2.15 (TC), U3.7 (CEP), U3.10 (CET)
/~BLOCK: U1.1 (~MR), U2.1 (~MR), U3.1 (~MR), U4.11 (O4), U5.11 (Cp), U8.2 (C)
/~BYTE: U1.2 (CP), U2.2 (CP), U3.2 (CP), U4.9 (O6), U7.2
/~CE: U6.30 (~CE), U7.4
/~RD: J1.24, U6.32 (~OE)
/~WR: J1.23, U6.5 (~WE)
/~Y0: J1.29, U4.4 (E1)
GND: BT1.2 (-), C1.2, C2.2, C3.2, C4.2, C5.2, J1.3, J1.4, J1.21, J1.22, J1.35, J1.36, U1.3 (D0), U1.4 (D1), U1.5 (D2), U1.6 (D3), U1.8 (GND), U2.3 (D0), U2.4 (D1), U2.5 (D2), U2.6 (D3), U2.8 (GND), U3.3 (D0), U3.4 (D1), U3.5 (D2), U3.6 (D3), U3.8 (GND), U4.1 (A0), U4.5 (E2), U4.8 (GND), U5.1 (OE), U5.10 (GND), U6.24 (GND), U7.3 (GND), U8.3 (GND)
unnamed: C1.1, R1.2
VBUS: C2.1, C3.1, C4.1, DA1.1 (A), J1.1, J1.2, JP1.1 (A), U1.7 (CEP), U1.9 (~PE), U1.10 (CET), U1.16 (VCC), U2.9 (~PE), U2.16 (VCC), U3.9 (~PE), U3.16 (VCC), U4.16 (VCC), U5.20 (VCC), U8.5 (VCC)
VMEM: C5.1, DA1.3 (K), R1.1, R2.1, U6.8 (VCC), U7.5 (VCC)

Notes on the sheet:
TANDY 102/200 SYSTEM BUS
+5VDC
BUS_A15
INTR
BUS_A14
ALE
~{INTA}
CLK
(**) A18 must be on pin 6 for 256k or 128k compatibility A17 must be on pin 9 for 128k compatibility
CR2032 - 7-13 years, 4.1mm thick: BT1 = Keystone 3034 C1 = TAJC227K010RNJ - 6032-28 220u 10v CR2016 - 3-7 years, 1.7mm thick: BT1 = Keystone 3028 C1 = TLJW157M010R0200 - 6032-15 150u 10v 128k: U8=DNP JP1=CLOSE U6=AS6C1008 256k: U8=DNP JP1=CLOSE U6=AS6C2008A 512k: U8=1G79 or 1G80 JP1=OPEN U6=AS6C4008
GND
IO/~{M}
CR2016
(or 1G80)
VDD
BUS BUS BUS (A) ~{YO} _A8 _A9 _A10 -> ~{BLOCK} ~{BYTE} Function L X X X X X X X H X X X X X X X L X X X X H L H L L -> L H Select BLOCK # from BANK 0 H L H L H -> L H Select BLOCK # from BANK 1 H L H H X -> H L Read or Write BYTE ~{BLOCK} L: sets A0-A9 to 0, updates A10-A18 from AD0-AD7 & BUS_A10 H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
RESET
(*) A17 must be opposite AD7 for 128k compatibility
This version is like the original DATAPAC wrt: * HC138 -> active-low ~{BLOCK} & ~{BYTE} * 3 x HC161 counter * HC374 (HC574) latch 1G79 & 1G32 added to support 512k.
(**)
BUS_A11
BUS_A13
(*)
BUS_A12

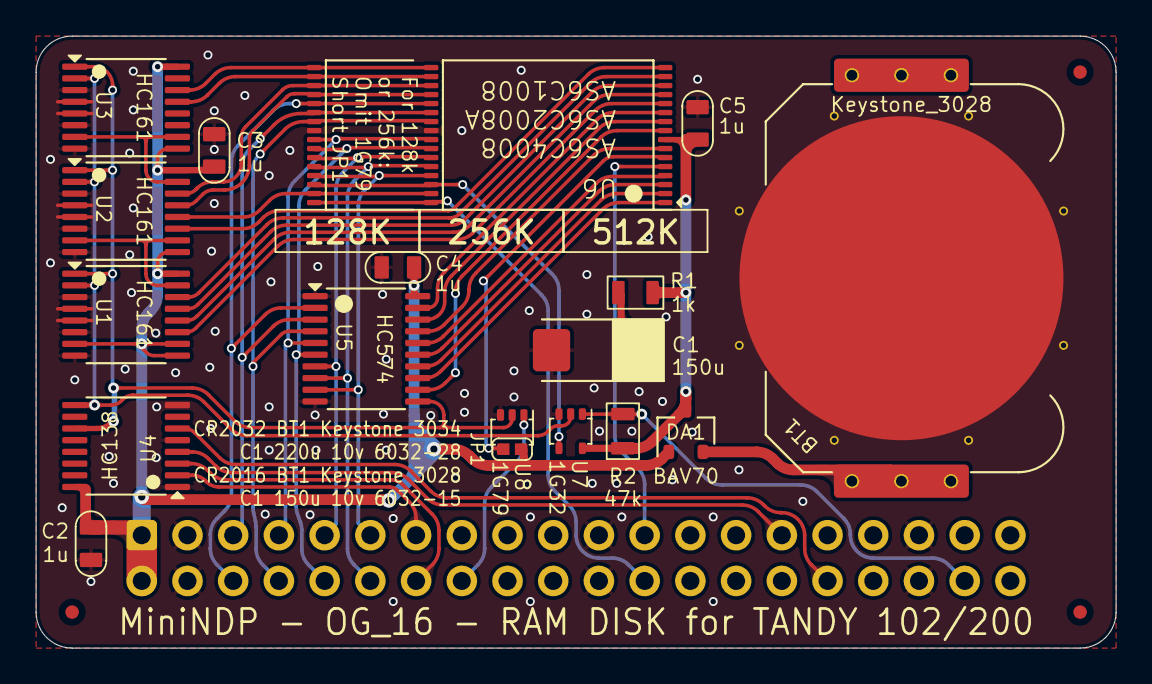
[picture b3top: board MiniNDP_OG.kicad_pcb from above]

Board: 2 copper layers, 60.0 x 34.0 mm, 23 parts (1 on the bottom side), 45 nets.

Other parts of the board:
F3, F3#2, F3#3: Fiducial_0.75_1.5
